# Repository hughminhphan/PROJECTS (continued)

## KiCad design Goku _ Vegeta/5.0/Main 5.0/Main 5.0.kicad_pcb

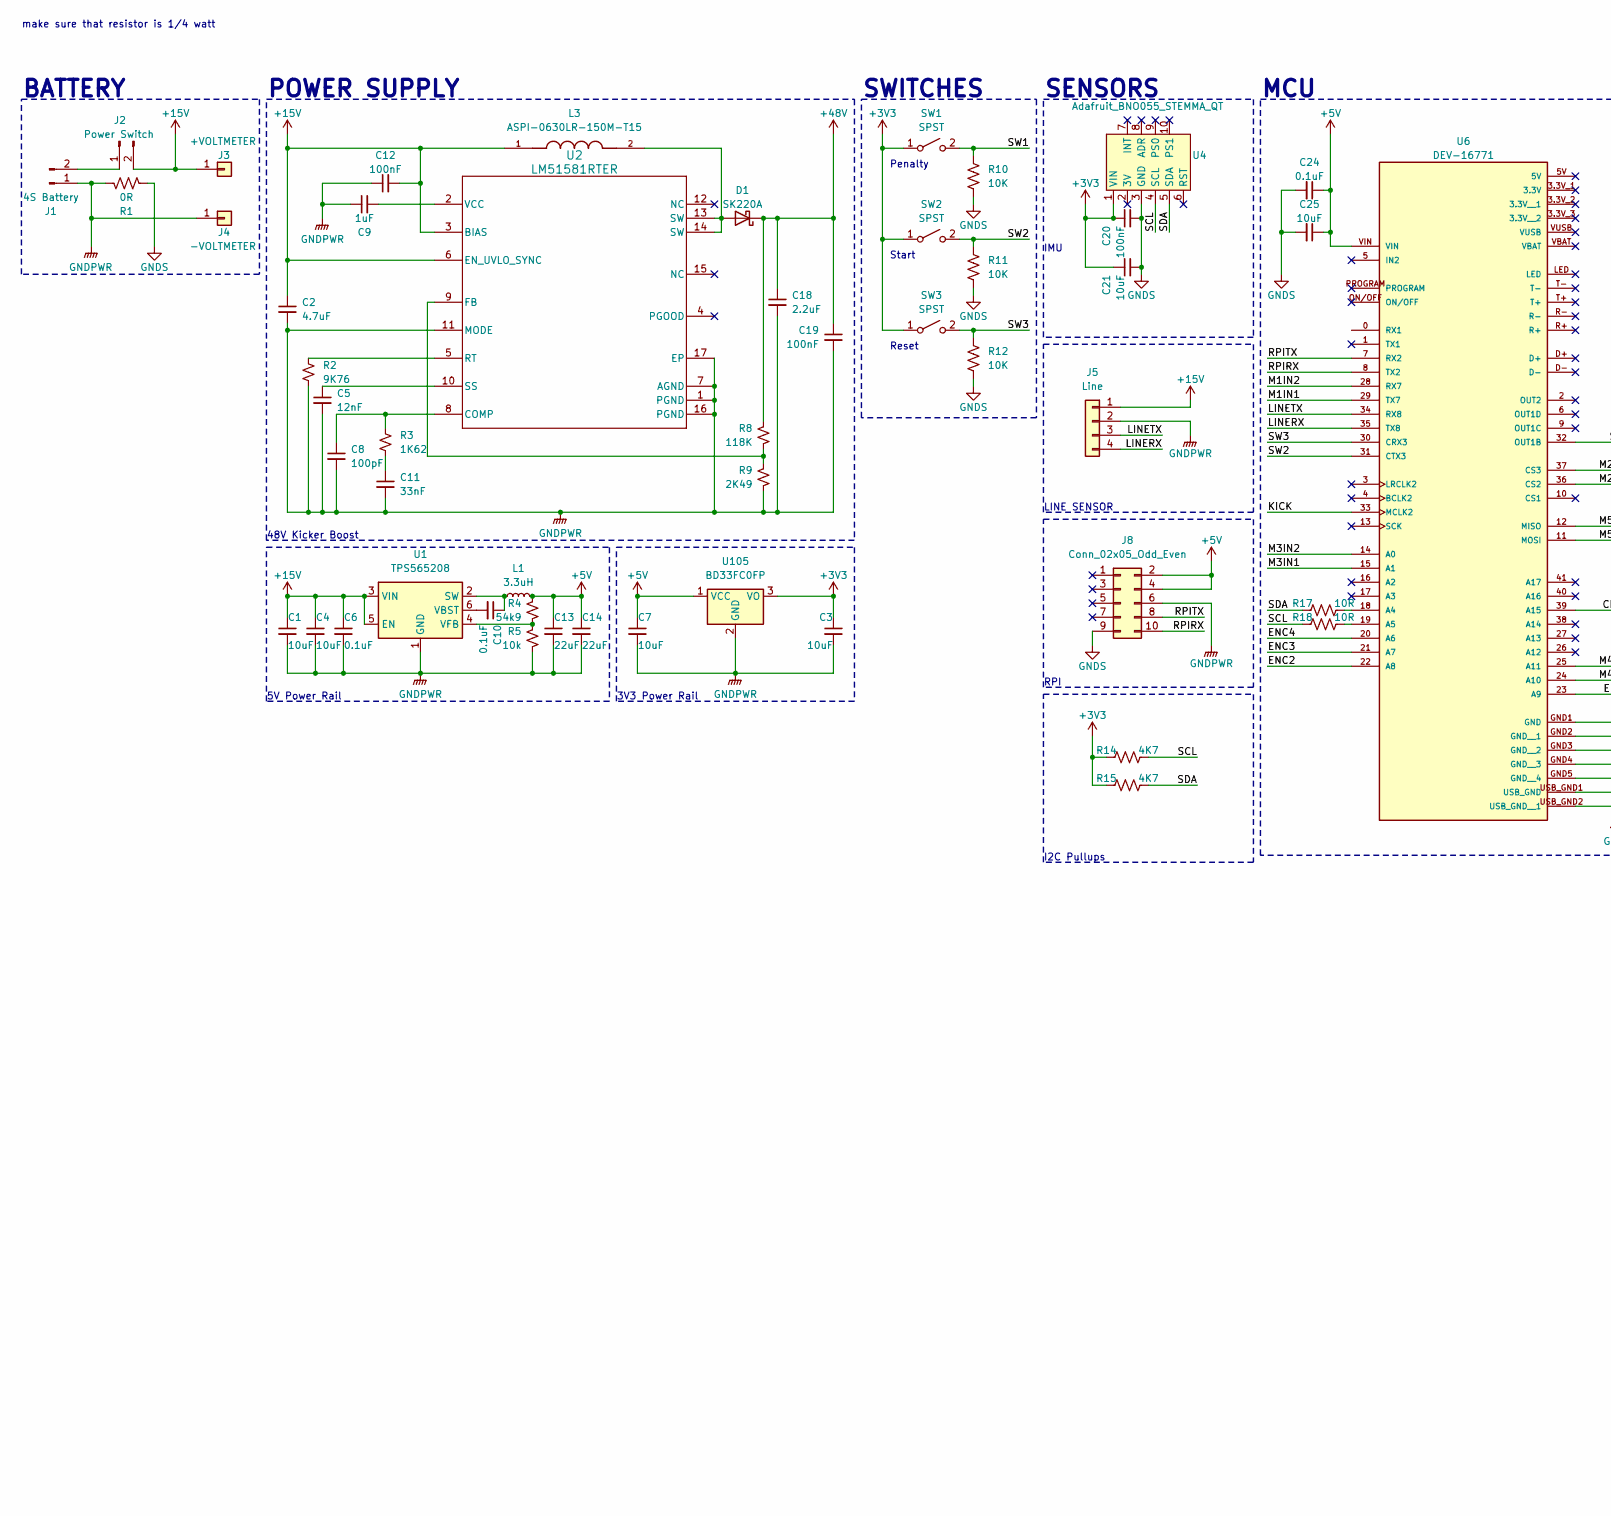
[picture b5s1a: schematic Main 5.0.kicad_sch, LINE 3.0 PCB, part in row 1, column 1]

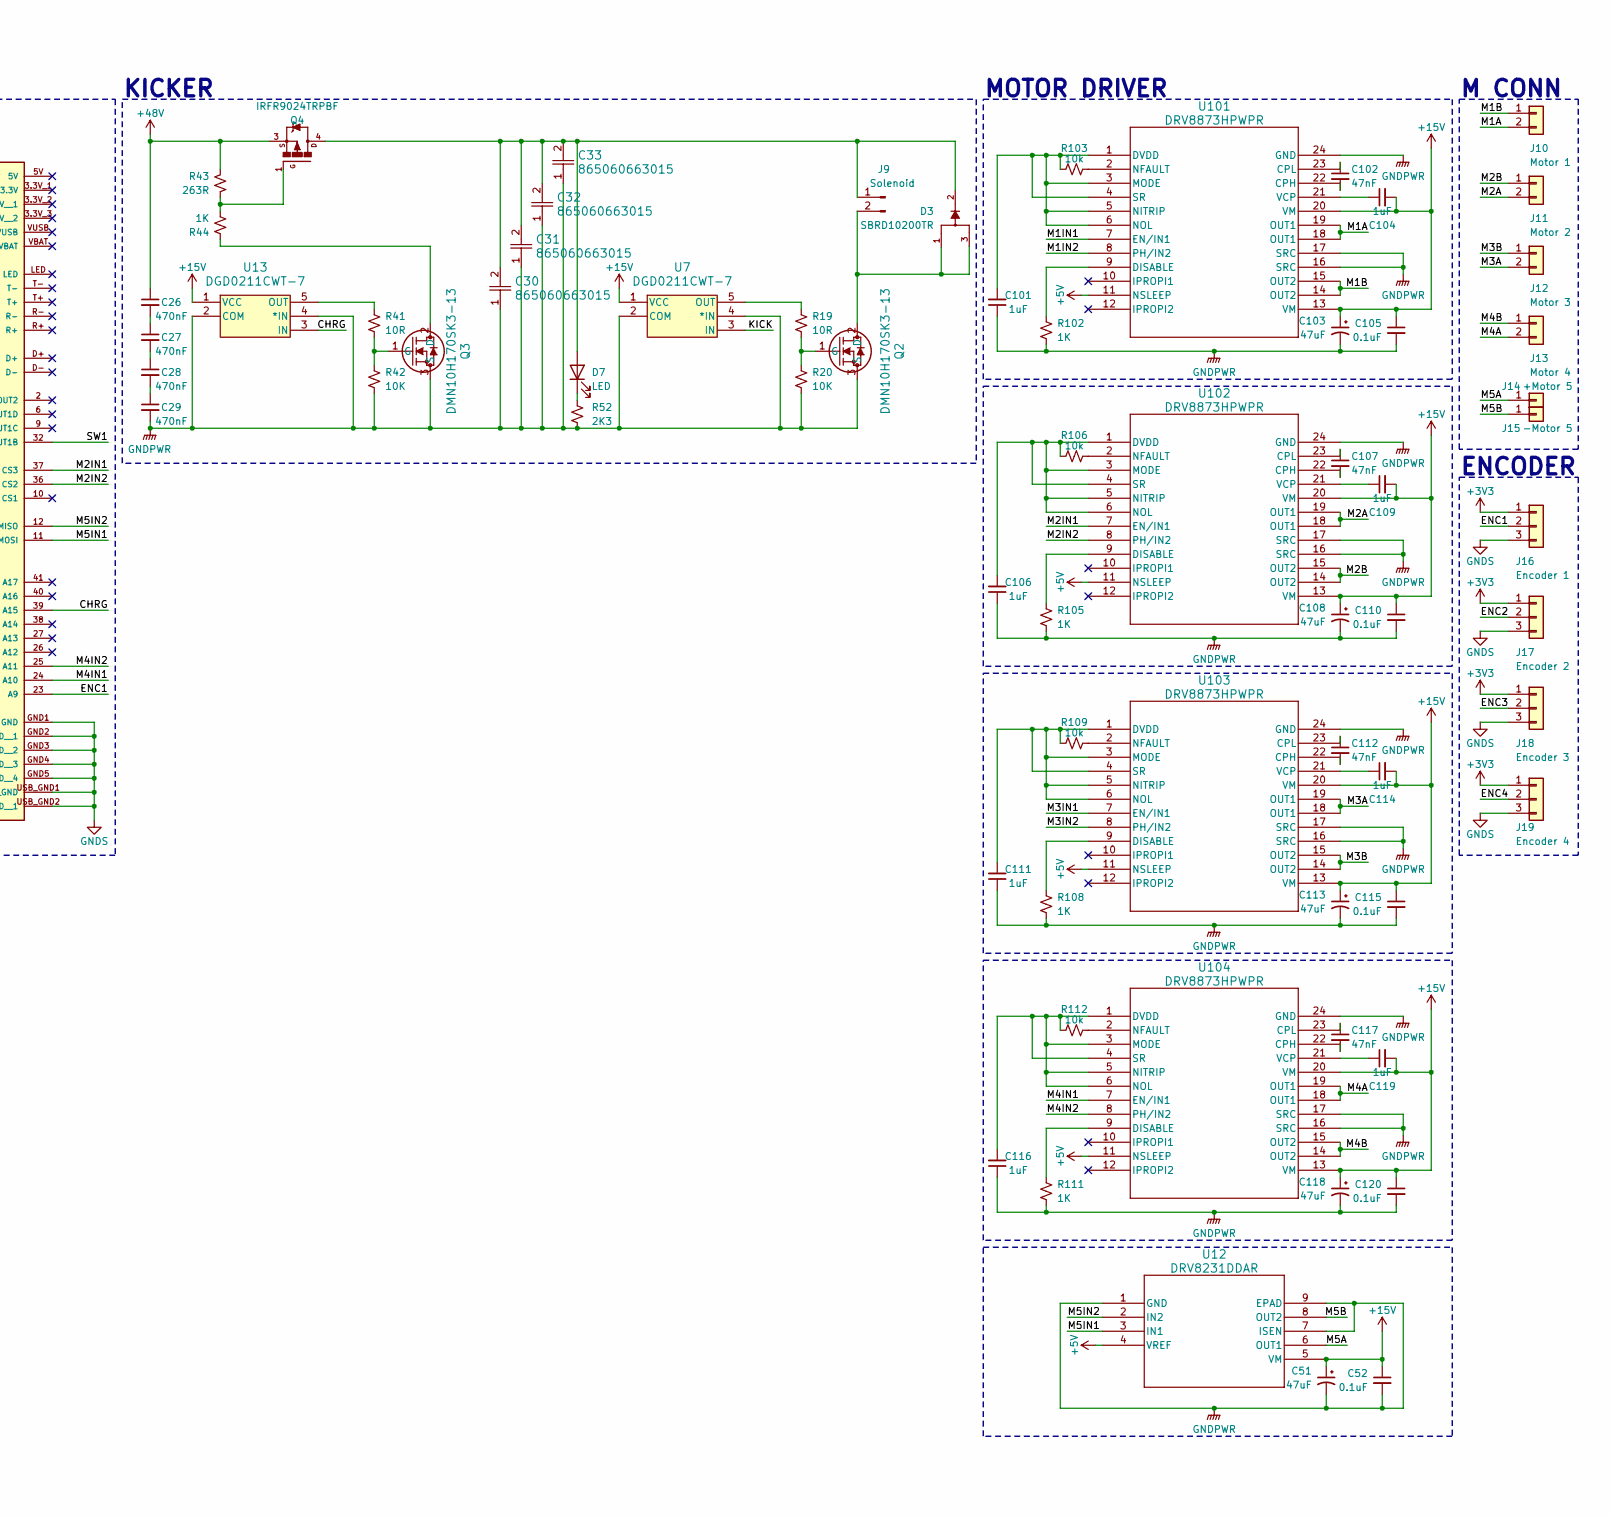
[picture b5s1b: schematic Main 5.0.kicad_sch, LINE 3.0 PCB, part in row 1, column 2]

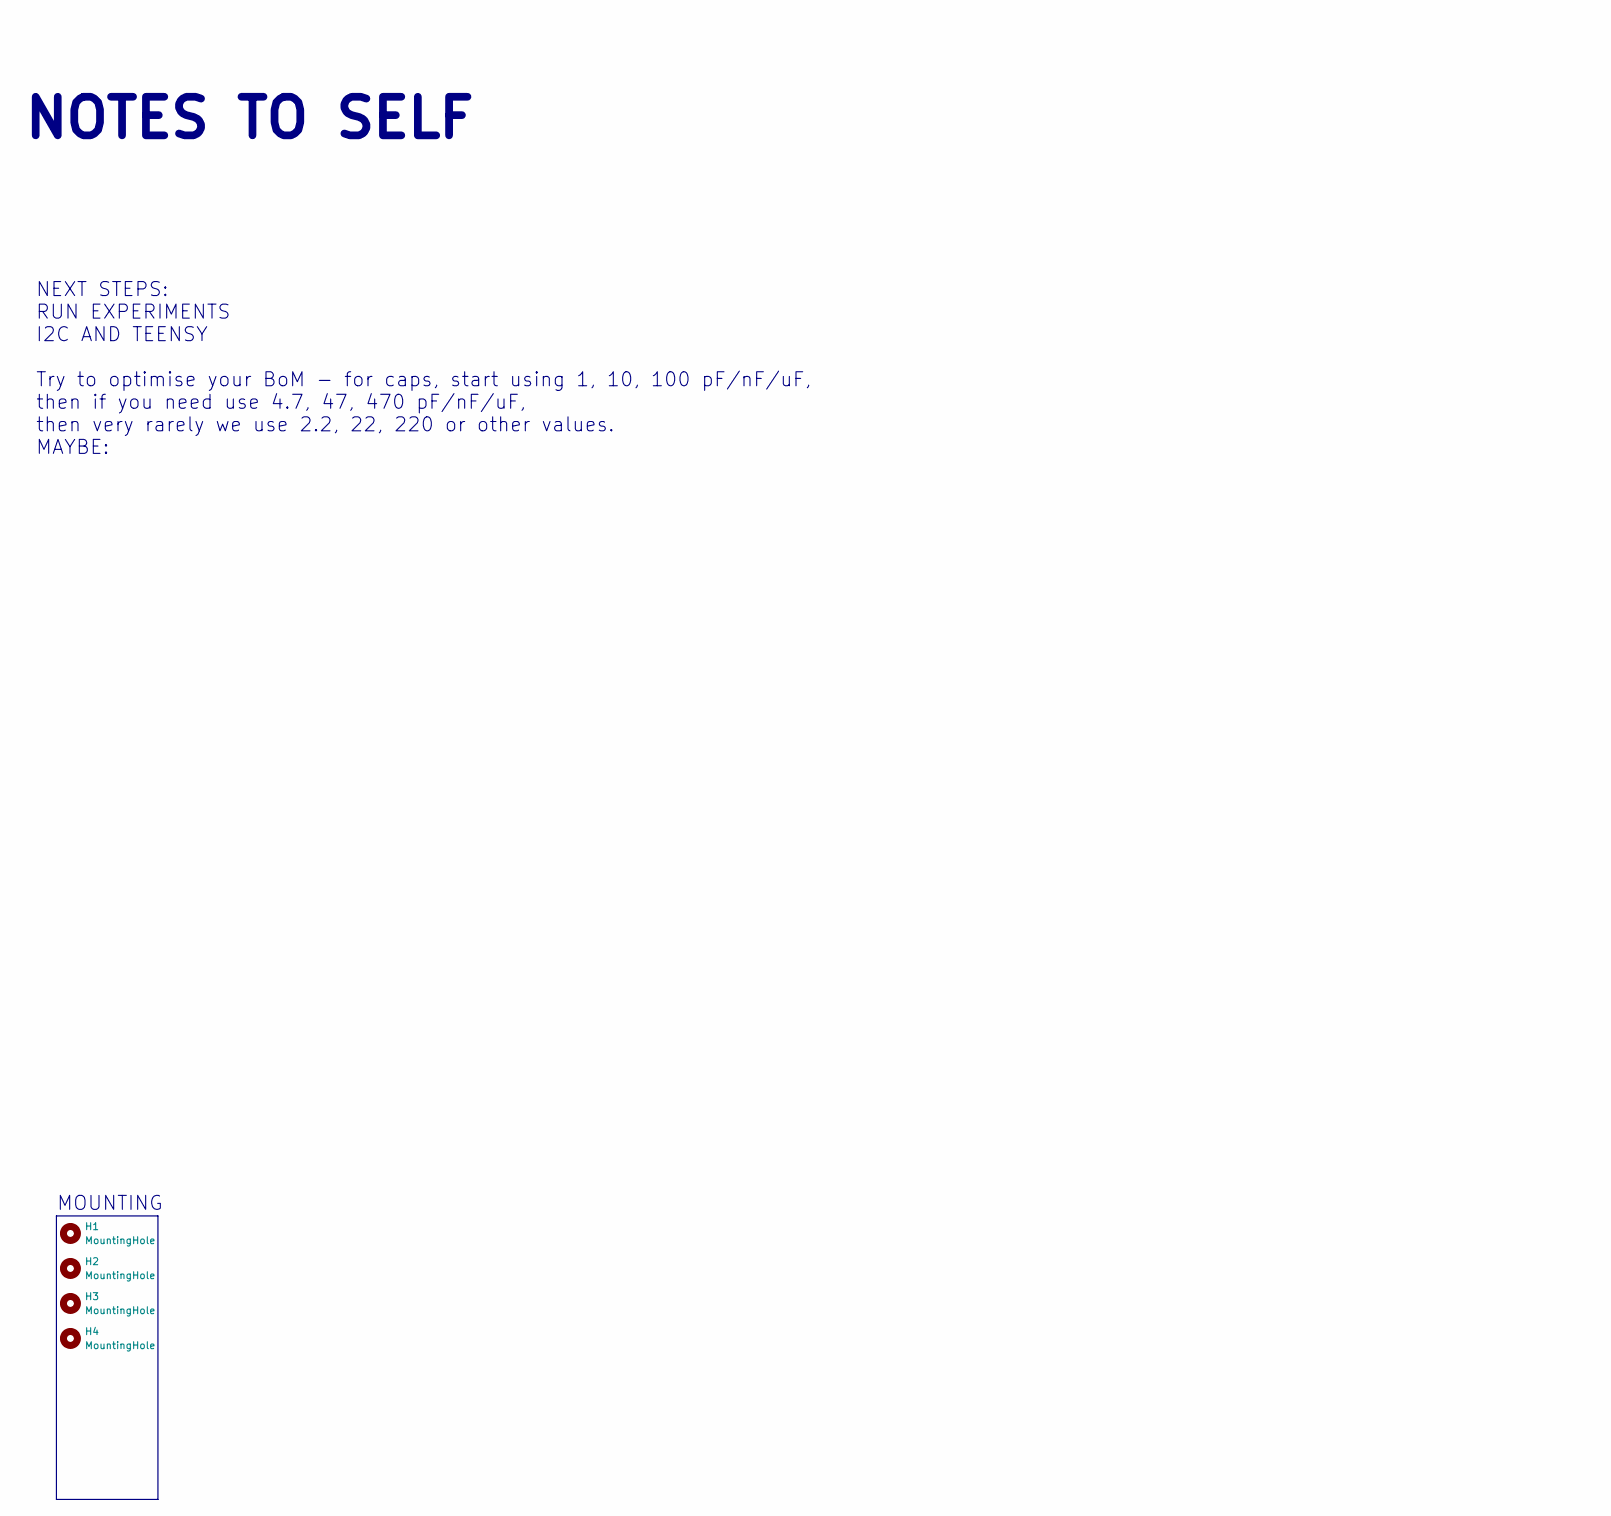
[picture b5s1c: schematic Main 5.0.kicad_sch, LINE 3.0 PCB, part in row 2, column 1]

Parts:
C1, C3, C4, C7: 10uF; C_0805_2012Metric
C2: 4.7uF; C_0805_2012Metric
C5: 12nF; C_0402_1005Metric
C6, C10, C24, C52, C105, C110, C115, C120: 0.1uF; C_0603_1608Metric
C8: 100pF; C_0805_2012Metric
C9, C101, C104, C106, C109, C111, C114, C116, C119: 1uF; C_0603_1608Metric
C11: 33nF; C_0402_1005Metric
C12, C19: 100nF; C_0805_2012Metric
C13, C14: 22uF; C_0603_1608Metric
C18: 2.2uF; C_1210_3225Metric
C20: 100nF; C_0603_1608Metric
C21, C25: 10uF; C_0603_1608Metric
C26, C27, C28, C29: 470nF; C_0603_1608Metric
C30, C31, C32, C33: 865060663015; CAP_WCAP-ASLL_16p0X17p0_WRE
C51, C103, C108, C113, C118: 47uF; CP_Elec_6.3x5.9
C102, C107, C112, C117: 47nF; C_0603_1608Metric
D1: SK220A; D_SMA
D3: SBRD10200TR; DPAK228P1005X240-4N; PARTREV A
D7: LED; LED_0603_1608Metric
H1, H2, H3, H4: MountingHole; MountingHole_2.2mm_M2
J1: 4S Battery; AMASS_XT30U-M_1x02_P5.0mm_Vertical
J2: Power Switch; AMASS_XT30U-F_1x02_P5.0mm_Vertical
J3: +VOLTMETER; SolderWirePad_1x01_SMD_1x2mm
J4: -VOLTMETER; SolderWirePad_1x01_SMD_1x2mm
J5: Line; JST_XH_B4B-XH-A_1x04_P2.50mm_Vertical
J8: Conn_02x05_Odd_Even; PinSocket_2x05_P2.54mm_Vertical
J9: Solenoid; AMASS_XT30U-M_1x02_P5.0mm_Vertical
J10: Motor 1; AMASS_XT30U-F_1x02_P5.0mm_Vertical
J11: Motor 2; AMASS_XT30U-F_1x02_P5.0mm_Vertical
J12: Motor 3; AMASS_XT30U-F_1x02_P5.0mm_Vertical
J13: Motor 4; AMASS_XT30U-F_1x02_P5.0mm_Vertical
J14: +Motor 5; SolderWirePad_1x01_SMD_1x2mm
J15: -Motor 5; SolderWirePad_1x01_SMD_1x2mm
J16: Encoder 1; JST_XH_B3B-XH-A_1x03_P2.50mm_Vertical
J17: Encoder 2; JST_XH_B3B-XH-A_1x03_P2.50mm_Vertical
J18: Encoder 3; JST_XH_B3B-XH-A_1x03_P2.50mm_Vertical
J19: Encoder 4; JST_XH_B3B-XH-A_1x03_P2.50mm_Vertical
L1: 3.3uH; MPXV1D0840
L3: ASPI-0630LR-150M-T15; IND_ASPI-0630LR-150M-T15; PARTREV B
Q2, Q3: DMN10H170SK3-13; QNMOS1G2D3S_TO252DPAK_DIO
Q4: IRFR9024TRPBF; DPAK
R1: 0R; R_1210_3225Metric
R2: 9K76; R_0402_1005Metric
R3: 1K62; R_0402_1005Metric
R4: 54k9; R_0402_1005Metric
R5: 10k; R_0402_1005Metric
R8: 118K; R_0603_1608Metric
R9: 2K49; R_0402_1005Metric
R10, R11, R12, R20, R42: 10K; R_0603_1608Metric
R14, R15: 4K7; R_0603_1608Metric
R17, R18, R19, R41: 10R; R_0603_1608Metric
R43: 263R; R_0603_1608Metric
R44, R102, R105, R108, R111: 1K; R_0603_1608Metric
R52: 2K3; R_0402_1005Metric
R103, R106, R109, R112: 10k; R_0603_1608Metric
SW1, SW2, SW3: SPST; SW_PUSH_6mm_H4.3mm
U1: TPS565208; SOT-23-6
U2: LM51581RTER; WQFN-16-1EP_3x3mm_P0.5mm_EP1.68x1.68mm_ThermalVias
U4: Adafruit_BNO055_STEMMA_QT; Adafruit IMU BNO055
U6: DEV-16771; MODULE_DEV-16771; PARTREV 4.1
U7, U13: DGD0211CWT-7; TSOT25-TH_DIO
U12: DRV8231DDAR; SOIC8_DDA_TEX
U101, U102, U103, U104: DRV8873HPWPR; PWP24_TEX
U105: BD33FC0FP; TO-252-2

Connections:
+3V3: C3.1, C20.1, C21.1, J16.1, J17.1, J18.1, J19.1, R14.1, R15.1, SW1.1 (A), SW2.1 (A), SW3.1 (A), U4.1 (VIN), U105.3 (VO)
+5V: C7.1, C13.1, C14.1, C24.1, C25.1, J8.2, J8.4, L1.2, R4.1, U6.VIN, U12.4 (VREF), U101.11 (NSLEEP), U102.11 (NSLEEP), U103.11 (NSLEEP), U104.11 (NSLEEP), U105.1 (VCC)
+15V: C1.1, C2.1, C4.1, C6.1, C12.2, C51.1, C52.1, C103.1, C104.2, C105.1, C108.1, C109.2, C110.1, C113.1, C114.2, C115.1, C118.1, C119.2, C120.1, J2.2, J3.1, J5.1, L3.1, U1.3 (VIN), U1.5 (EN), U2.3 (BIAS), U2.6 (EN_UVLO_SYNC), U7.1 (VCC), U12.5 (VM), U13.1 (VCC), U101.13 (VM), U101.20 (VM), U102.13 (VM), U102.20 (VM), U103.13 (VM), U103.20 (VM), U104.13 (VM), U104.20 (VM)
+48V: C18.1, C19.1, C26.1, D1.1 (K), Q4.3, R8.1, R43.1
/CHRG: U6.39 (A15), U13.3 (IN)
/ENC1: J16.2, U6.23 (A9)
/ENC2: J17.2, U6.22 (A8)
/ENC3: J18.2, U6.21 (A7)
/ENC4: J19.2, U6.20 (A6)
/KICK: U6.33 (MCLK2), U7.3 (IN)
/LINERX: J5.4, U6.35 (TX8)
/LINETX: J5.3, U6.34 (RX8)
/M1A: J10.2, U101.18 (OUT1), U101.19 (OUT1)
/M1B: J10.1, U101.14 (OUT2), U101.15 (OUT2)
/M1IN1: U6.29 (TX7), U101.7 (EN/IN1)
/M1IN2: U6.28 (RX7), U101.8 (PH/IN2)
/M2A: J11.2, U102.18 (OUT1), U102.19 (OUT1)
/M2B: J11.1, U102.14 (OUT2), U102.15 (OUT2)
/M2IN1: U6.37 (CS3), U102.7 (EN/IN1)
/M2IN2: U6.36 (CS2), U102.8 (PH/IN2)
/M3A: J12.2, U103.18 (OUT1), U103.19 (OUT1)
/M3B: J12.1, U103.14 (OUT2), U103.15 (OUT2)
/M3IN1: U6.15 (A1), U103.7 (EN/IN1)
/M3IN2: U6.14 (A0), U103.8 (PH/IN2)
/M4A: J13.2, U104.18 (OUT1), U104.19 (OUT1)
/M4B: J13.1, U104.14 (OUT2), U104.15 (OUT2)
/M4IN1: U6.24 (A10), U104.7 (EN/IN1)
/M4IN2: U6.25 (A11), U104.8 (PH/IN2)
/M5A: J14.1, U12.6 (OUT1)
/M5B: J15.1, U12.8 (OUT2)
/M5IN1: U6.11 (MOSI), U12.3 (IN1)
/M5IN2: U6.12 (MISO), U12.2 (IN2)
/RPIRX: J8.10, U6.8 (TX2)
/RPITX: J8.8, U6.7 (RX2)
/SCL: R14.2, R18.1, U4.4 (SCL)
/SDA: R15.2, R17.1, U4.5 (SDA)
/SW1: R10.1, SW1.2 (B), U6.32 (OUT1B)
/SW2: R11.1, SW2.2 (B), U6.31 (CTX3)
/SW3: R12.1, SW3.2 (B), U6.30 (CRX3)
GNDPWR: C1.2, C2.2, C3.2, C4.2, C5.2, C6.2, C7.2, C8.2, C9.1, C11.2, C12.1, C13.2, C14.2, C18.2, C19.2, C29.2, C30.1, C31.1, C32.1, C33.1, C51.2, C52.2, C101.1, C103.2, C105.2, C106.1, C108.2, C110.2, C111.1, C113.2, C115.2, C116.1, C118.2, C120.2, J1.1, J4.1, J5.2, J8.6, Q2.3 (S), Q3.3 (S), R1.2, R2.2, R5.2, R9.2, R20.2, R42.2, R52.2, R102.2, R105.2, R108.2, R111.2, U1.1 (GND), U2.1 (PGND), U2.7 (AGND), U2.11 (MODE), U2.16 (PGND), U2.17 (EP), U7.2 (COM), U7.4 (*IN), U12.1 (GND), U12.7 (ISEN), U12.9 (EPAD), U12.EPAD, U13.2 (COM), U13.4 (*IN), U101.16 (SRC), U101.17 (SRC), U101.24 (GND), U101.EPAD, U102.16 (SRC), U102.17 (SRC), U102.24 (GND), U102.EPAD, U103.16 (SRC), U103.17 (SRC), U103.24 (GND), U103.EPAD, U104.16 (SRC), U104.17 (SRC), U104.24 (GND), U104.EPAD, U105.2 (GND)
GNDS: C20.2, C21.2, C24.2, C25.2, J8.9, J16.3, J17.3, J18.3, J19.3, R1.1, R10.2, R11.2, R12.2, U4.3 (GND), U6.GND1 (GND), U6.GND2 (GND__1), U6.GND3 (GND__2), U6.GND4 (GND__3), U6.GND5 (GND__4), U6.USB_GND1 (USB_GND), U6.USB_GND2 (USB_GND__1)
unnamed: C11.1, R3.2
unnamed: C26.2, C27.1
unnamed: C27.2, C28.1
unnamed: C28.2, C29.1
unnamed: D1.2 (A), L3.2, U2.13 (SW), U2.14 (SW)
unnamed: C30.2, C31.2, C32.2, C33.2, D3.2, D7.2 (A), J9.1, Q4.4
unnamed: D7.1 (K), R52.1
unnamed: J1.2, J2.1
unnamed: D3.1, D3.3, J9.2, Q2.2 (D)
unnamed: Q2.1 (G), R19.2, R20.1
unnamed: Q3.2 (D), R44.1
unnamed: Q3.1 (G), R41.2, R42.1
unnamed: Q4.1, R43.2, R44.2
unnamed: C10.1, L1.1, U1.2 (SW)
unnamed: C10.2, U1.6 (VBST)
unnamed: R4.2, R5.1, U1.4 (VFB)
unnamed: C8.1, R3.1, U2.8 (COMP)
unnamed: R8.2, R9.1, U2.9 (FB)
unnamed: R2.1, U2.5 (RT)
unnamed: C5.1, U2.10 (SS)
unnamed: C9.2, U2.2 (VCC)
unnamed: R17.2, U6.18 (A4)
unnamed: R18.2, U6.19 (A5)
unnamed: R19.1, U7.5 (OUT)
unnamed: R41.1, U13.5 (OUT)
unnamed: C102.2, U101.22 (CPH)
unnamed: C102.1, U101.23 (CPL)
unnamed: R102.1, U101.9 (DISABLE)
unnamed: C101.2, R103.1, U101.1 (DVDD), U101.3 (MODE), U101.4 (SR), U101.5 (NITRIP), U101.6 (NOL)
unnamed: R103.2, U101.2 (NFAULT)
unnamed: C104.1, U101.21 (VCP)
unnamed: C107.2, U102.22 (CPH)
unnamed: C107.1, U102.23 (CPL)
unnamed: R105.1, U102.9 (DISABLE)
unnamed: C106.2, R106.1, U102.1 (DVDD), U102.3 (MODE), U102.4 (SR), U102.5 (NITRIP), U102.6 (NOL)
unnamed: R106.2, U102.2 (NFAULT)
unnamed: C109.1, U102.21 (VCP)
unnamed: C112.2, U103.22 (CPH)
unnamed: C112.1, U103.23 (CPL)
unnamed: R108.1, U103.9 (DISABLE)
unnamed: C111.2, R109.1, U103.1 (DVDD), U103.3 (MODE), U103.4 (SR), U103.5 (NITRIP), U103.6 (NOL)
unnamed: R109.2, U103.2 (NFAULT)
unnamed: C114.1, U103.21 (VCP)
unnamed: C117.2, U104.22 (CPH)
unnamed: C117.1, U104.23 (CPL)
unnamed: R111.1, U104.9 (DISABLE)
unnamed: C116.2, R112.1, U104.1 (DVDD), U104.3 (MODE), U104.4 (SR), U104.5 (NITRIP), U104.6 (NOL)
unnamed: R112.2, U104.2 (NFAULT)
unnamed: C119.1, U104.21 (VCP)

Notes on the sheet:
NOTES TO SELF
MOUNTING
NEXT STEPS: RUN EXPERIMENTS I2C AND TEENSY Try to optimise your BoM - for caps, start using 1, 10, 100 pF/nF/uF, then if you need use 4.7, 47, 470 pF/nF/uF, then very rarely we use 2.2, 22, 220 or other values. MAYBE:
Penalty
ENCODER
3V3 Power Rail
BATTERY
POWER SUPPLY
IMU
SENSORS
make sure that resistor is 1/4 watt
RPI
MOTOR DRIVER
48V Kicker Boost
Start
Reset
I2C Pullups
M CONN
SWITCHES
MCU
5V Power Rail
LINE SENSOR
KICKER

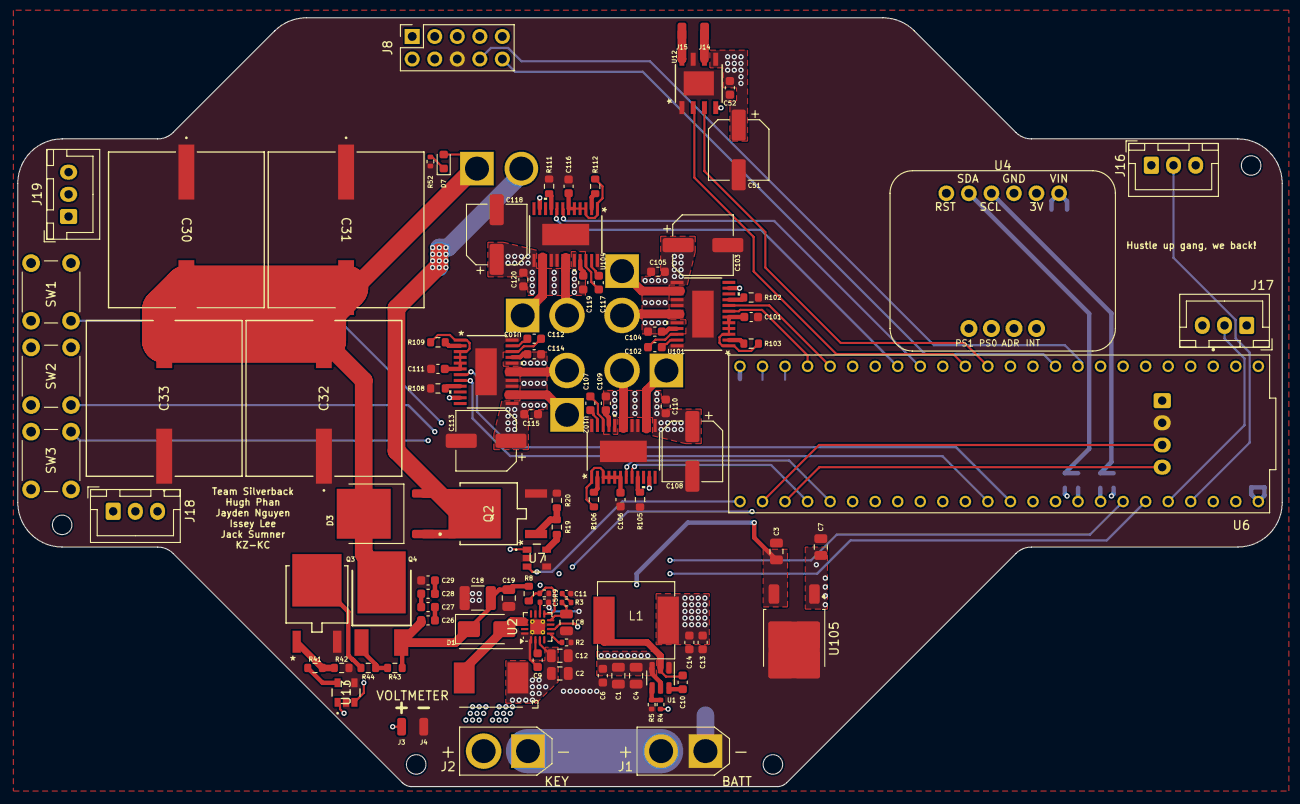
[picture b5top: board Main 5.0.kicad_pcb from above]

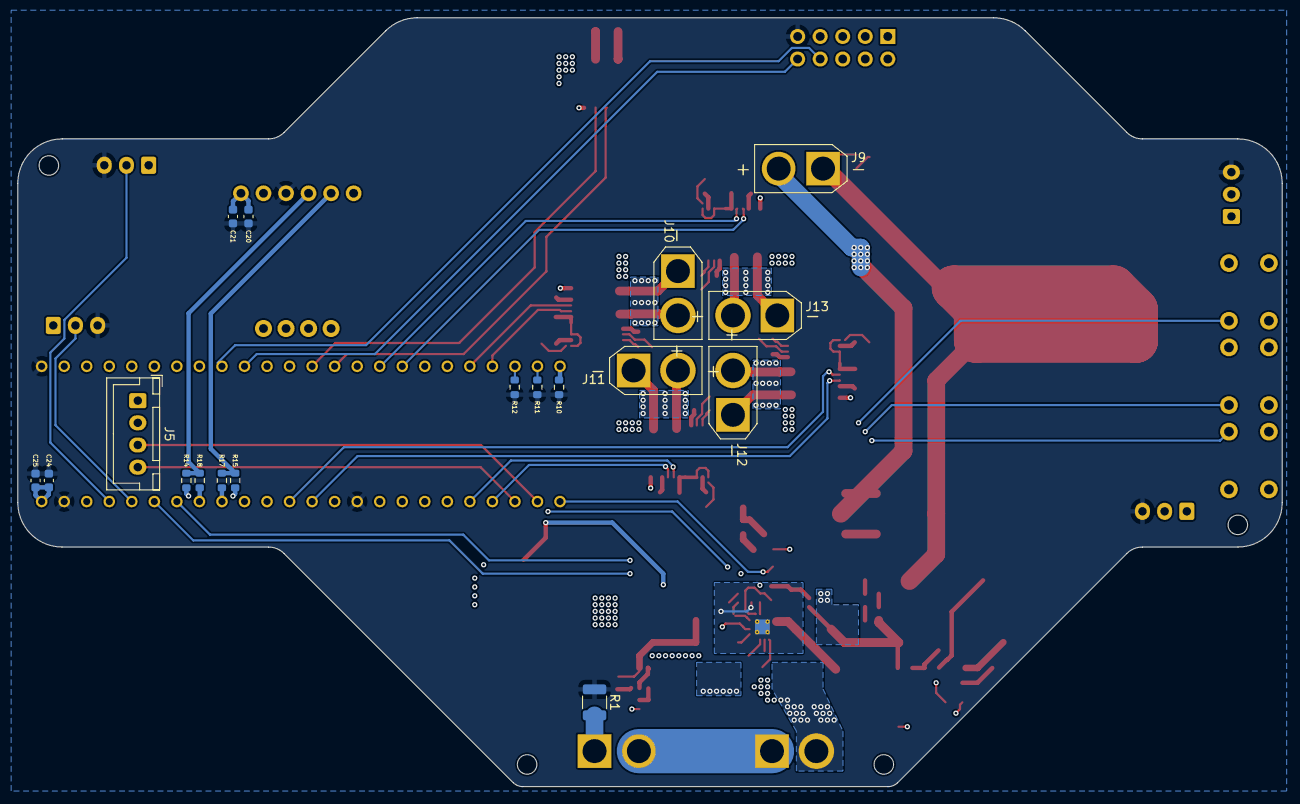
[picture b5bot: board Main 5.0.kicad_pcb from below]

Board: 4 copper layers, 142.5 x 86.6 mm, 123 parts (18 on the bottom side), 90 nets.
